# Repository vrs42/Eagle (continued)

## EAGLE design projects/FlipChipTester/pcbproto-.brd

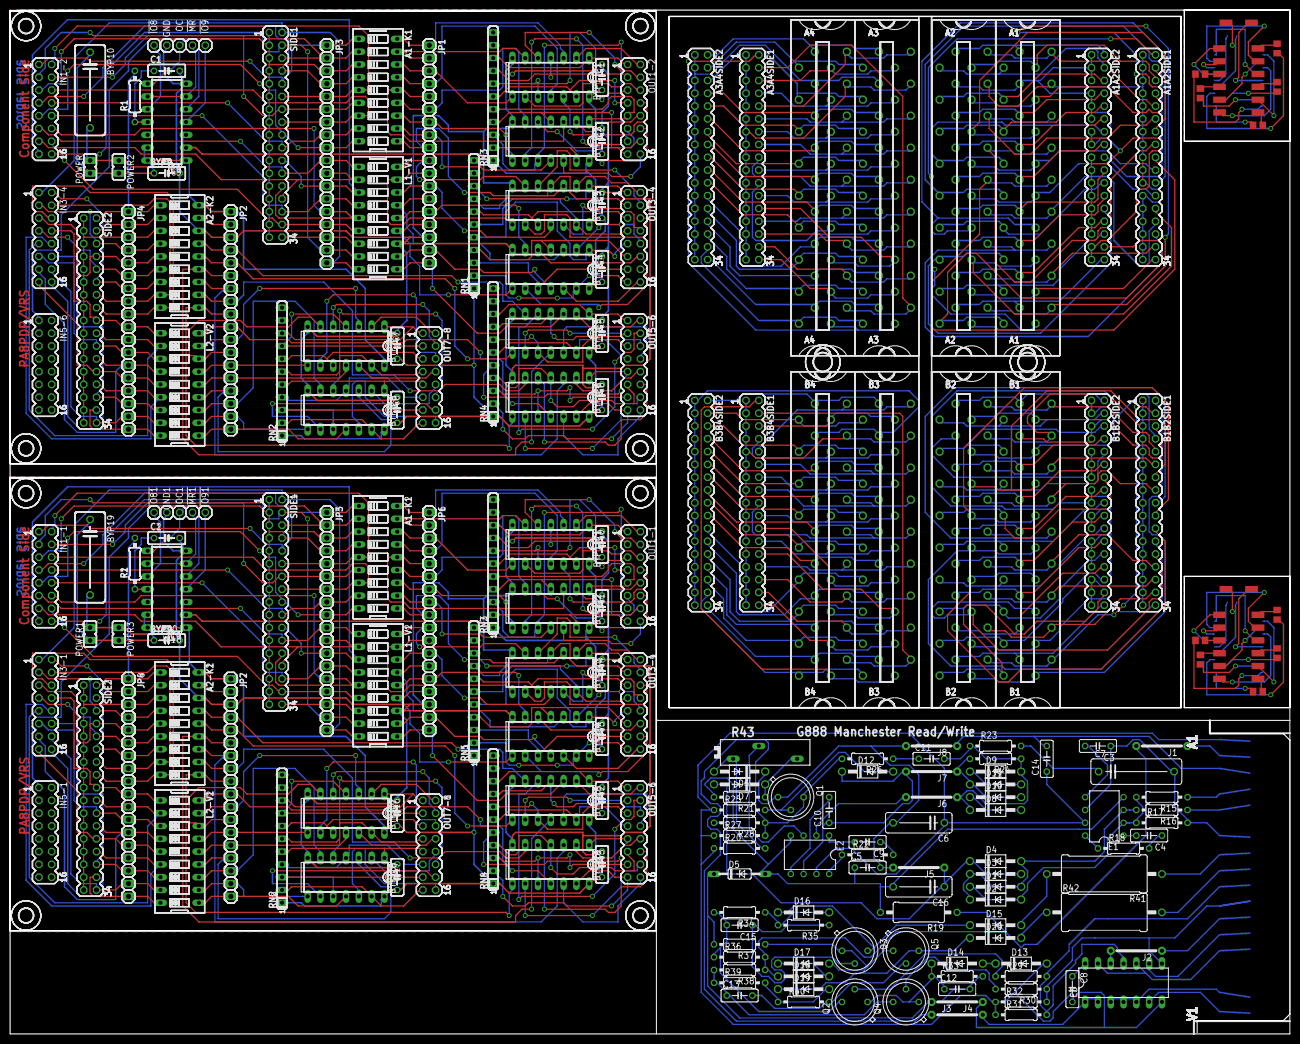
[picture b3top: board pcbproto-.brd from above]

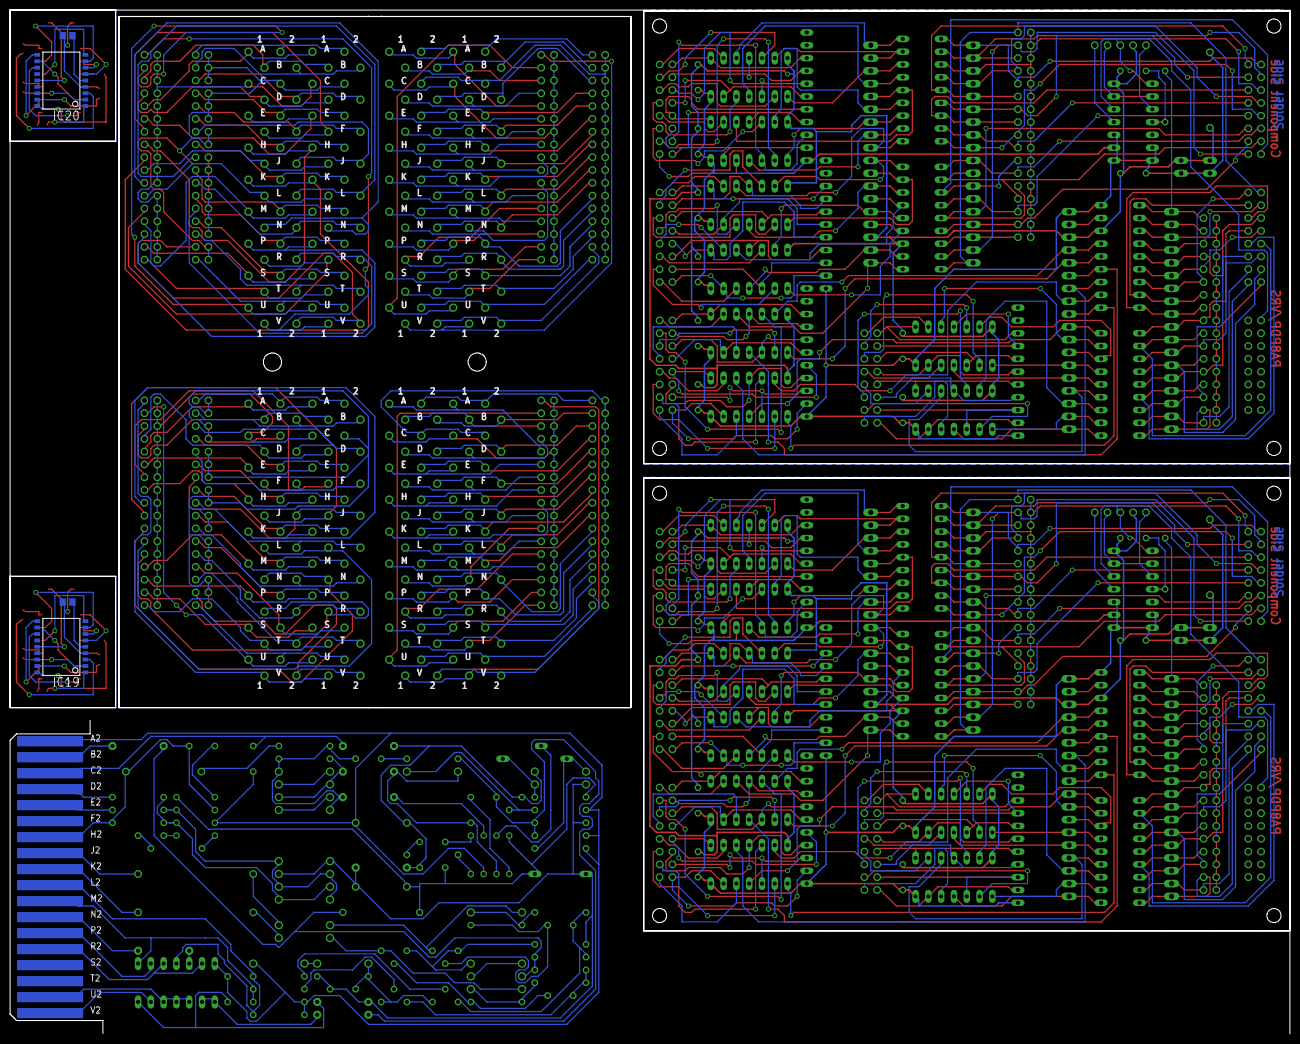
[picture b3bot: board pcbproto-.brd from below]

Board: 2 copper layers, 254.0 x 203.2 mm, 246 parts (4 on the bottom side), 520 nets.

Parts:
!IO8, !IO81: !IO8; 1X01
!IO9, !IO91: !IO9; 1X01
!MR, !MR1: !MR; 1X01
A1, A2, A3, A4: H807
A1-K1, A1-K2: A1-K1; EDG-09
A1A2SIDE1, A1A2SIDE2, A3A4SIDE1, A3A4SIDE2: MA17-2
A2-K1, A2-K2: A2-K2; EDG-09
B1, B2, B3, B4: H807
B1B2SIDE1, B1B2SIDE2, B3B4SIDE1, B3B4SIDE2: MA17-2
BYP1, BYP2, BYP3, BYP4, BYP5, BYP6, BYP7, BYP8, BYP9, BYP11, BYP12, BYP13, BYP14, BYP15, BYP16, BYP17, BYP18, BYP20: 0.1uf; C050-025X075
BYP10, BYP19: 100uf 25V; C150-064X183
C1, C2: 0.1uf; C050-025X075
C3, C5, C8, C10, C11, C12, C14: .01uf; C050-025X075
C4, C9: .22uf; C050-025X075
C6, C16: 6.8uf 35V; C102-043X133
C7: .01uf MYLAR 10%; C150-054X183
C13, C15: .1uf; C050-025X075
D1, D2, D3, D4, D8, D9, D10, D11, D12: 1N3606; DO41-10
D5: 1N753A; DO35Z10
D6, D7, D13, D14, D17, D18: 1N645; DO41-10
D15, D16, D19, D20: D670; DO41-10
E1, E2: MC1709; DIL08
E3: 7400N; DIL14
GND, GND1: GND; 1X01
IC1, IC2, IC3, IC4, IC5, IC6, IC7, IC8, IC10, IC11, IC12, IC13, IC14, IC15, IC16, IC17: 74LS125N; DIL14
IC9, IC18: 74LS10N; DIL14
IC19, IC20: PIC16F627SO; SO-18W
IN1-1, IN1-2, IN3-1, IN3-4, IN5-1, IN5-6: MA08-2
J1, J2, J3, J4, J5, J6, J7, J8: J10MM; 10
JP1, JP2, JP3, JP4, JP5, JP6, JP7, JP8: 1X18
L1-V1, L1-V2: L1-V1; EDG-09
L2-V1, L2-V2: L2-V2; EDG-09
OC, OC1: OC; 1X01
OUT1-1, OUT1-2, OUT3-1, OUT3-4, OUT5-1, OUT5-6, OUT7-1, OUT7-8: MA08-2
PAD1, PAD2, PAD3, PAD4, PAD5, PAD6, PAD7, PAD8, PAD9, PAD10, PAD11, PAD12, PAD13, PAD14, PAD15, PAD16, PAD17, PAD18, PAD19, PAD20, PAD21, PAD22, PAD23, PAD24, PAD25, PAD26, PAD27, PAD28: SMD2
POWER, POWER1, POWER2, POWER3: POWER; JP1
Q1: 2n3009B; TO39
Q2, Q4: MPS6534; TO39
Q3, Q5: MM1008; TO39
R1, R2, R20, R21, R27, R31, R32, R36, R37, R38: 1K; 0207/10
R3, R4, R5, R6, R7, R8, R9, R10, R11, R12, R13, R14: R0805
R15, R16: 220; 0207/10
R17: 22K; 0207/10
R18, R22: 1.5K; 0207/10
R19: 330 1/2W; 0411/15
R23, R25: 4.7K; 0207/10
R24, R26: 470K; 0207/10
R28: 3K; 0207/10
R29, R30, R33: 470; 0207/10
R34, R39: 750; 0207/10
R35, R40: 560; 0207/10
R41, R42: 68 2W; P0817/22
R43: 5K; PT-SPIN
RN1, RN2, RN3, RN4, RN5, RN6, RN7, RN8: SIL11
SIDE1, SIDE2, SIDE3, SIDE4: MA17-2
U$1, U$2, U$3, U$4, U$7, U$8, U$9, U$10: 2,8
U$5, U$6: 3,6
U$11: EDGE-1; EDGE-CON1

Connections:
!C1: IC19.17, R3.1
!C2: IC19.18, R4.1
!C3: IC19.1, R5.1
!C4: IC19.2, R6.1
!C5: IC19.3, R7.1
!C11: IC20.17, R9.1
!C21: IC20.18, R10.1
!C31: IC20.1, R11.1
!C41: IC20.2, R12.1
!C51: IC20.3, R13.1
!COL1: PAD4.1, R3.2
!COL2: PAD3.1, R4.2
!COL3: PAD7.1, R5.2
!COL4: PAD9.1, R6.2
!COL5: PAD12.1, R7.2
!COL11: PAD20.1, R9.2
!COL21: PAD17.1, R10.2
!COL31: PAD21.1, R11.2
!COL41: PAD23.1, R12.2
!COL51: PAD24.1, R13.2
!IO8: !IO8.1, IC9.10
!IO9: !IO9.1, IC9.4
!IO81: !IO81.1, IC18.10
!IO91: !IO91.1, IC18.4
!MR: !MR.1, IC9.6, IC9.9
!MR1: !MR1.1, IC18.6, IC18.9
!STEM: IC19.4, PAD15.1, R8.1
!STEM1: IC20.4, PAD27.1, R14.1
-15V: D18.C, J1.2, R19.1, R36.2, R38.1
A1: A1-K1.1, IN1-2.1, JP3.1, SIDE1.10
A2: A2-K2.1, JP4.1, R1.2, SIDE2.2
A3: A1-K2.1, IN1-1.1, JP5.1, SIDE4.10
A4: A2-K1.1, JP8.1, R2.2, SIDE3.2
B1: A1-K1.2, IN1-2.3, JP3.2, SIDE1.6
B2: A2-K2.2, JP4.2, SIDE2.4
B3: A1-K2.2, IN1-1.3, JP5.2, SIDE4.6
B4: A2-K1.2, JP8.2, SIDE3.4
C1: A1-K1.3, IN1-2.5, JP3.3, SIDE1.1, SIDE1.3, SIDE1.5, SIDE1.7, SIDE1.9, SIDE1.11, SIDE1.13, SIDE1.15, SIDE1.17, SIDE1.19, SIDE1.21, SIDE1.23, SIDE1.25, SIDE1.27, SIDE1.29, SIDE1.31, SIDE1.33
C2: A2-K2.3, JP4.3, SIDE2.1, SIDE2.3, SIDE2.5, SIDE2.7, SIDE2.9, SIDE2.11, SIDE2.13, SIDE2.15, SIDE2.17, SIDE2.19, SIDE2.21, SIDE2.23, SIDE2.25, SIDE2.27, SIDE2.29, SIDE2.31, SIDE2.33
C3: A1-K2.3, IN1-1.5, JP5.3, SIDE4.1, SIDE4.3, SIDE4.5, SIDE4.7, SIDE4.9, SIDE4.11, SIDE4.13, SIDE4.15, SIDE4.17, SIDE4.19, SIDE4.21, SIDE4.23, SIDE4.25, SIDE4.27, SIDE4.29, SIDE4.31, SIDE4.33
C4: A2-K1.3, JP8.3, SIDE3.1, SIDE3.3, SIDE3.5, SIDE3.7, SIDE3.9, SIDE3.11, SIDE3.13, SIDE3.15, SIDE3.17, SIDE3.19, SIDE3.21, SIDE3.23, SIDE3.25, SIDE3.27, SIDE3.29, SIDE3.31, SIDE3.33
D: R15.1, U$11.D2
D1: A1-K1.4, IN1-2.7, JP3.4, SIDE1.8
D2: A2-K2.4, IN3-4.3, JP4.4, SIDE2.6
D3: A1-K2.4, IN1-1.7, JP5.4, SIDE4.8
D4: A2-K1.4, IN3-1.3, JP8.4, SIDE3.6
E: R16.1, U$11.E2
E1: A1-K1.5, IN1-2.2, JP3.5, SIDE1.12
E2: A2-K2.5, IN3-4.5, JP4.5, SIDE2.8
E3: A1-K2.5, IN1-1.2, JP5.5, SIDE4.12
E4: A2-K1.5, IN3-1.5, JP8.5, SIDE3.8
F1: A1-K1.6, IN1-2.4, JP3.6, SIDE1.14
F2: A2-K2.6, IN3-4.7, JP4.6, SIDE2.10
F3: A2-K1.6, IN3-1.7, JP8.6, SIDE3.10
F4: A1-K2.6, IN1-1.4, JP5.6, SIDE4.14
GND: A2-K2.16, BYP1.2, BYP2.2, BYP3.2, BYP4.2, BYP5.2, BYP6.2, BYP7.2, BYP8.2, BYP9.2, BYP10.2, C1.2, GND.1, IC1.7, IC2.7, IC3.7, IC4.7, IC5.7, IC6.7, IC7.7, IC8.7, IC9.7, JP1.16, JP2.3, L1-V1.12, POWER.1, POWER2.1
GND1: A2-K1.16, BYP11.2, BYP12.2, BYP13.2, BYP14.2, BYP15.2, BYP16.2, BYP17.2, BYP18.2, BYP19.2, BYP20.2, C2.2, GND1.1, IC10.7, IC11.7, IC12.7, IC13.7, IC14.7, IC15.7, IC16.7, IC17.7, IC18.7, JP6.16, JP7.3, L1-V2.12, POWER1.1, POWER3.1
GND2: IC19.5, R8.2
GND3: IC20.5, R14.2
GND4: C5.2, C6.2, C8.2, C12.2, C14.2, C16.1, D3.A, D4.C, D5.C, D6.C, D7.A, E3.7, J4.1, J4.2, J5.1, J5.2, J8.1, J8.2, Q1.1, R28.2, R33.2, R37.2, U$11.C2
H: C3.1, C7.2, E1.6, R17.2, U$11.H2
H1: A1-K1.7, IN1-2.6, JP3.7, SIDE1.16
H2: A2-K2.7, IN3-4.2, JP4.7, SIDE2.12
H3: A1-K2.7, IN1-1.6, JP5.7, SIDE4.16
H4: A2-K1.7, IN3-1.2, JP8.7, SIDE3.12
J: R41.1, U$11.J2
J1: A1-K1.8, IN1-2.8, JP3.8, SIDE1.20
J2: A2-K2.8, IN3-4.4, JP4.8, SIDE2.14
J3: A1-K2.8, IN1-1.8, JP5.8, SIDE4.20
J4: A2-K1.8, IN3-1.4, JP8.8, SIDE3.14
K: R42.2, U$11.K2
K1: A1-K1.9, IN1-2.9, JP3.9, SIDE1.18
K2: A2-K2.9, IN3-4.6, JP4.9, SIDE2.16
K3: A2-K1.9, IN3-1.6, JP8.9, SIDE3.16
K4: A1-K2.9, IN1-1.9, JP5.9, SIDE4.18
L: E3.11, R29.2, R31.2, U$11.L2
L1: IN1-2.11, JP3.10, L1-V1.1, SIDE1.24
L2: IN3-4.8, JP4.10, L2-V2.1, SIDE2.18
L3: IN1-1.11, JP5.10, L1-V2.1, SIDE4.24
L4: IN3-1.8, JP8.10, L2-V1.1, SIDE3.18
M: E3.8, R30.1, R32.2, U$11.M2
M1: IN1-2.13, JP3.11, L1-V1.2, SIDE1.28
M2: IN3-4.9, JP4.11, L2-V2.2, SIDE2.20
M3: IN1-1.13, JP5.11, L1-V2.2, SIDE4.28
M4: IN3-1.9, JP8.11, L2-V1.2, SIDE3.20
N: J2.1, U$11.N2
N1: IN1-2.15, JP3.12, L1-V1.3, SIDE1.22
N2: IN3-4.11, JP4.12, L2-V2.3, SIDE2.22
N3: IN3-1.11, JP8.12, L2-V1.3, SIDE3.22
N4: IN1-1.15, JP5.12, L1-V2.3, SIDE4.22
unnamed: B1.C2, B1B2SIDE2.1, B1B2SIDE2.3, B1B2SIDE2.5, B1B2SIDE2.7, B1B2SIDE2.9, B1B2SIDE2.11, B1B2SIDE2.13, B1B2SIDE2.15, B1B2SIDE2.17, B1B2SIDE2.19, B1B2SIDE2.21, B1B2SIDE2.23, B1B2SIDE2.25, B1B2SIDE2.27, B1B2SIDE2.29, B1B2SIDE2.31, B1B2SIDE2.33, B2.C2
unnamed: B1.A2, B1B2SIDE2.2, B2.A2
unnamed: B1.B2, B1B2SIDE2.4, B2.B2
unnamed: B1.D2, B1B2SIDE2.6, B2.D2
unnamed: B1.E2, B1B2SIDE2.8, B2.E2
unnamed: B1.F2, B1B2SIDE2.10, B2.F2
unnamed: B1.H2, B1B2SIDE2.12, B2.H2
unnamed: B1.J2, B1B2SIDE2.14, B2.J2
unnamed: B1.K2, B1B2SIDE2.16, B2.K2
unnamed: B1.L2, B1B2SIDE2.18, B2.L2
unnamed: B1.M2, B1B2SIDE2.20, B2.M2
unnamed: B1.N2, B1B2SIDE2.22, B2.N2
unnamed: B1.P2, B1B2SIDE2.24, B2.P2
unnamed: B1.R2, B1B2SIDE2.26, B2.R2
unnamed: B1.S2, B1B2SIDE2.28, B2.S2
unnamed: B1.T2, B1B2SIDE2.30, B2.T2
unnamed: B1.U2, B1B2SIDE2.34, B2.U2
unnamed: B1.V2, B1B2SIDE2.32, B2.V2
unnamed: B1.A1, B1B2SIDE1.10, B2.A1
unnamed: B1.B1, B1B2SIDE1.6, B2.B1
unnamed: B1.D1, B1B2SIDE1.8, B2.D1
unnamed: B1.E1, B1B2SIDE1.12, B2.E1
unnamed: B1.F1, B1B2SIDE1.14, B2.F1
unnamed: B1.H1, B1B2SIDE1.16, B2.H1
unnamed: B1.J1, B1B2SIDE1.20, B2.J1
unnamed: B1.K1, B1B2SIDE1.18, B2.K1
unnamed: B1.L1, B1B2SIDE1.24, B2.L1
unnamed: B1.M1, B1B2SIDE1.28, B2.M1
unnamed: B1.N1, B1B2SIDE1.22, B2.N1
unnamed: B1.P1, B1B2SIDE1.30, B2.P1
unnamed: B1.R1, B1B2SIDE1.26, B2.R1
unnamed: B1.S1, B1B2SIDE1.32, B2.S1
unnamed: B1.T1, B1B2SIDE1.34, B2.T1
unnamed: B1.U1, B1B2SIDE1.4, B2.U1
unnamed: B1.V1, B1B2SIDE1.2, B2.V1
unnamed: B1.C1, B1B2SIDE1.1, B1B2SIDE1.3, B1B2SIDE1.5, B1B2SIDE1.7, B1B2SIDE1.9, B1B2SIDE1.11, B1B2SIDE1.13, B1B2SIDE1.15, B1B2SIDE1.17, B1B2SIDE1.19, B1B2SIDE1.21, B1B2SIDE1.23, B1B2SIDE1.25, B1B2SIDE1.27, B1B2SIDE1.29, B1B2SIDE1.31, B1B2SIDE1.33, B2.C1
unnamed: A1.C2, A1A2SIDE2.1, A1A2SIDE2.3, A1A2SIDE2.5, A1A2SIDE2.7, A1A2SIDE2.9, A1A2SIDE2.11, A1A2SIDE2.13, A1A2SIDE2.15, A1A2SIDE2.17, A1A2SIDE2.19, A1A2SIDE2.21, A1A2SIDE2.23, A1A2SIDE2.25, A1A2SIDE2.27, A1A2SIDE2.29, A1A2SIDE2.31, A1A2SIDE2.33, A2.C2
unnamed: A1.A2, A1A2SIDE2.2, A2.A2
unnamed: A1.B2, A1A2SIDE2.4, A2.B2
unnamed: A1.D2, A1A2SIDE2.6, A2.D2
unnamed: A1.E2, A1A2SIDE2.8, A2.E2
unnamed: A1.F2, A1A2SIDE2.10, A2.F2
unnamed: A1.H2, A1A2SIDE2.12, A2.H2
unnamed: A1.J2, A1A2SIDE2.14, A2.J2
unnamed: A1.K2, A1A2SIDE2.16, A2.K2
unnamed: A1.L2, A1A2SIDE2.18, A2.L2
unnamed: A1.M2, A1A2SIDE2.20, A2.M2
unnamed: A1.N2, A1A2SIDE2.22, A2.N2
unnamed: A1.P2, A1A2SIDE2.24, A2.P2
unnamed: A1.R2, A1A2SIDE2.26, A2.R2
unnamed: A1.S2, A1A2SIDE2.28, A2.S2
unnamed: A1.T2, A1A2SIDE2.30, A2.T2
unnamed: A1.U2, A1A2SIDE2.34, A2.U2
unnamed: A1.V2, A1A2SIDE2.32, A2.V2
unnamed: A1.A1, A1A2SIDE1.10, A2.A1
unnamed: A1.B1, A1A2SIDE1.6, A2.B1
unnamed: A1.D1, A1A2SIDE1.8, A2.D1
unnamed: A1.E1, A1A2SIDE1.12, A2.E1
unnamed: A1.F1, A1A2SIDE1.14, A2.F1
unnamed: A1.H1, A1A2SIDE1.16, A2.H1
unnamed: A1.J1, A1A2SIDE1.20, A2.J1
unnamed: A1.K1, A1A2SIDE1.18, A2.K1
unnamed: A1.L1, A1A2SIDE1.24, A2.L1
unnamed: A1.M1, A1A2SIDE1.28, A2.M1
unnamed: A1.N1, A1A2SIDE1.22, A2.N1
unnamed: A1.P1, A1A2SIDE1.30, A2.P1
unnamed: A1.R1, A1A2SIDE1.26, A2.R1
unnamed: A1.S1, A1A2SIDE1.32, A2.S1
unnamed: A1.T1, A1A2SIDE1.34, A2.T1
unnamed: A1.U1, A1A2SIDE1.4, A2.U1
unnamed: A1.V1, A1A2SIDE1.2, A2.V1
unnamed: A1.C1, A1A2SIDE1.1, A1A2SIDE1.3, A1A2SIDE1.5, A1A2SIDE1.7, A1A2SIDE1.9, A1A2SIDE1.11, A1A2SIDE1.13, A1A2SIDE1.15, A1A2SIDE1.17, A1A2SIDE1.19, A1A2SIDE1.21, A1A2SIDE1.23, A1A2SIDE1.25, A1A2SIDE1.27, A1A2SIDE1.29, A1A2SIDE1.31, A1A2SIDE1.33, A2.C1
unnamed: IC1.4, OUT1-2.3, RN3.8
unnamed: IC1.13, OUT1-2.7, RN3.6
unnamed: IC1.2, OUT1-2.2
unnamed: IC1.5, OUT1-2.4
unnamed: IC1.9, OUT1-2.6
unnamed: IC1.12, OUT1-2.8
unnamed: IC2.10, OUT1-2.13, RN3.3
unnamed: IC2.4, OUT1-2.11, RN3.4
unnamed: IC2.1, OUT1-2.9, RN3.5
unnamed: IC2.2, OUT1-2.10
unnamed: IC2.9, OUT1-2.14
unnamed: IC2.12, OUT1-2.16
unnamed: IC1.1, OUT1-2.1, RN3.9
unnamed: IC1.10, OUT1-2.5, RN3.7
unnamed: IC2.5, OUT1-2.12
unnamed: IC5.4, OUT5-6.3, RN4.8
unnamed: IC6.4, OUT5-6.11, RN4.4
unnamed: IC6.1, OUT5-6.9, RN4.5
unnamed: IC6.2, OUT5-6.10
unnamed: IC6.9, OUT5-6.14
unnamed: IC6.12, OUT5-6.16
unnamed: IC5.1, OUT5-6.1, RN4.9
unnamed: IC5.10, OUT5-6.5, RN4.7
unnamed: IC6.5, OUT5-6.12
unnamed: IC6.13, OUT5-6.15, RN4.2
unnamed: IC3.4, OUT3-4.3, RN1.8
unnamed: IC3.13, OUT3-4.7, RN1.6
unnamed: IC3.2, OUT3-4.2
unnamed: IC3.5, OUT3-4.4
unnamed: IC3.9, OUT3-4.6
unnamed: IC3.12, OUT3-4.8
unnamed: IC4.10, OUT3-4.13, RN1.3
unnamed: IC4.4, OUT3-4.11, RN1.4
unnamed: IC4.1, OUT3-4.9, RN1.5
unnamed: IC4.2, OUT3-4.10
unnamed: IC4.9, OUT3-4.14
unnamed: IC4.12, OUT3-4.16
unnamed: IC3.1, OUT3-4.1, RN1.9
unnamed: IC3.10, OUT3-4.5, RN1.7
unnamed: IC4.5, OUT3-4.12
unnamed: IC4.13, OUT3-4.15, RN1.2
unnamed: IC7.4, OUT7-8.3, RN2.8
unnamed: IC7.13, OUT7-8.7, RN2.6
unnamed: IC7.2, OUT7-8.2
unnamed: IC7.5, OUT7-8.4
unnamed: IC7.9, OUT7-8.6
unnamed: IC7.12, OUT7-8.8
unnamed: IC8.10, OUT7-8.13, RN2.3
unnamed: IC8.4, OUT7-8.11, RN2.4
unnamed: IC8.1, OUT7-8.9, RN2.5
unnamed: IC8.2, OUT7-8.10
unnamed: IC8.9, OUT7-8.14
unnamed: C1.1, IC9.11, R1.1
unnamed: IC10.4, OUT1-1.3, RN7.8
unnamed: IC10.13, OUT1-1.7, RN7.6
unnamed: IC10.2, OUT1-1.2
unnamed: IC10.5, OUT1-1.4
unnamed: IC10.9, OUT1-1.6
unnamed: IC10.12, OUT1-1.8
unnamed: IC11.10, OUT1-1.13, RN7.3
unnamed: IC11.4, OUT1-1.11, RN7.4
unnamed: IC11.1, OUT1-1.9, RN7.5
unnamed: IC11.2, OUT1-1.10
unnamed: IC11.9, OUT1-1.14
unnamed: IC11.12, OUT1-1.16
unnamed: IC5.13, OUT5-6.7, RN4.6
unnamed: IC2.13, OUT1-2.15, RN3.2
unnamed: IC5.2, OUT5-6.2
unnamed: IC5.5, OUT5-6.4
unnamed: IC5.9, OUT5-6.6
unnamed: IC5.12, OUT5-6.8
unnamed: IC6.10, OUT5-6.13, RN4.3
unnamed: A3.C2, A3A4SIDE2.1, A3A4SIDE2.3, A3A4SIDE2.5, A3A4SIDE2.7, A3A4SIDE2.9, A3A4SIDE2.11, A3A4SIDE2.13, A3A4SIDE2.15, A3A4SIDE2.17, A3A4SIDE2.19, A3A4SIDE2.21, A3A4SIDE2.23, A3A4SIDE2.25, A3A4SIDE2.27, A3A4SIDE2.29, A3A4SIDE2.31, A3A4SIDE2.33, A4.C2
unnamed: A3.A2, A3A4SIDE2.2, A4.A2
unnamed: A3.B2, A3A4SIDE2.4, A4.B2
unnamed: A3.D2, A3A4SIDE2.6, A4.D2
unnamed: A3.E2, A3A4SIDE2.8, A4.E2
unnamed: A3.F2, A3A4SIDE2.10, A4.F2
unnamed: A3.H2, A3A4SIDE2.12, A4.H2
unnamed: A3.J2, A3A4SIDE2.14, A4.J2
unnamed: A3.K2, A3A4SIDE2.16, A4.K2
unnamed: A3.L2, A3A4SIDE2.18, A4.L2
unnamed: A3.M2, A3A4SIDE2.20, A4.M2
unnamed: A3.N2, A3A4SIDE2.22, A4.N2
unnamed: A3.P2, A3A4SIDE2.24, A4.P2
unnamed: A3.R2, A3A4SIDE2.26, A4.R2
unnamed: A3.S2, A3A4SIDE2.28, A4.S2
unnamed: A3.T2, A3A4SIDE2.30, A4.T2
unnamed: A3.U2, A3A4SIDE2.34, A4.U2
unnamed: A3.V2, A3A4SIDE2.32, A4.V2
unnamed: A3.A1, A3A4SIDE1.10, A4.A1
unnamed: A3.B1, A3A4SIDE1.6, A4.B1
unnamed: A3.D1, A3A4SIDE1.8, A4.D1
unnamed: A3.E1, A3A4SIDE1.12, A4.E1
unnamed: A3.F1, A3A4SIDE1.14, A4.F1
unnamed: A3.H1, A3A4SIDE1.16, A4.H1
unnamed: A3.J1, A3A4SIDE1.20, A4.J1
unnamed: A3.K1, A3A4SIDE1.18, A4.K1
unnamed: A3.L1, A3A4SIDE1.24, A4.L1
unnamed: A3.M1, A3A4SIDE1.28, A4.M1
unnamed: A3.N1, A3A4SIDE1.22, A4.N1
unnamed: A3.P1, A3A4SIDE1.30, A4.P1
unnamed: A3.R1, A3A4SIDE1.26, A4.R1
unnamed: A3.S1, A3A4SIDE1.32, A4.S1
unnamed: A3.T1, A3A4SIDE1.34, A4.T1
unnamed: A3.U1, A3A4SIDE1.4, A4.U1
unnamed: A3.V1, A3A4SIDE1.2, A4.V1
unnamed: A3.C1, A3A4SIDE1.1, A3A4SIDE1.3, A3A4SIDE1.5, A3A4SIDE1.7, A3A4SIDE1.9, A3A4SIDE1.11, A3A4SIDE1.13, A3A4SIDE1.15, A3A4SIDE1.17, A3A4SIDE1.19, A3A4SIDE1.21, A3A4SIDE1.23, A3A4SIDE1.25, A3A4SIDE1.27, A3A4SIDE1.29, A3A4SIDE1.31, A3A4SIDE1.33, A4.C1
unnamed: IC8.12, OUT7-8.16
unnamed: IC7.1, OUT7-8.1, RN2.9
unnamed: IC7.10, OUT7-8.5, RN2.7
unnamed: IC8.5, OUT7-8.12
unnamed: IC8.13, OUT7-8.15, RN2.2
unnamed: IC10.1, OUT1-1.1, RN7.9
unnamed: IC10.10, OUT1-1.5, RN7.7
unnamed: IC11.5, OUT1-1.12
unnamed: IC11.13, OUT1-1.15, RN7.2
unnamed: IC12.4, OUT5-1.3, RN8.8
unnamed: IC12.13, OUT5-1.7, RN8.6
unnamed: IC12.2, OUT5-1.2
unnamed: IC12.5, OUT5-1.4
unnamed: IC12.9, OUT5-1.6
unnamed: IC12.12, OUT5-1.8
unnamed: IC13.10, OUT5-1.13, RN8.3
unnamed: IC13.4, OUT5-1.11, RN8.4
unnamed: IC13.1, OUT5-1.9, RN8.5
unnamed: IC13.2, OUT5-1.10
unnamed: IC13.9, OUT5-1.14
unnamed: IC13.12, OUT5-1.16
unnamed: IC12.1, OUT5-1.1, RN8.9
unnamed: IC12.10, OUT5-1.5, RN8.7
unnamed: IC13.5, OUT5-1.12
unnamed: IC13.13, OUT5-1.15, RN8.2
unnamed: IC14.4, OUT3-1.3, RN5.8
unnamed: IC14.13, OUT3-1.7, RN5.6
unnamed: IC14.2, OUT3-1.2
unnamed: IC14.5, OUT3-1.4
unnamed: IC14.9, OUT3-1.6
unnamed: IC14.12, OUT3-1.8
unnamed: IC15.10, OUT3-1.13, RN5.3
unnamed: IC15.4, OUT3-1.11, RN5.4
unnamed: IC15.1, OUT3-1.9, RN5.5
unnamed: IC15.2, OUT3-1.10
unnamed: IC15.9, OUT3-1.14
unnamed: IC15.12, OUT3-1.16
unnamed: IC14.1, OUT3-1.1, RN5.9
unnamed: IC14.10, OUT3-1.5, RN5.7
unnamed: IC15.5, OUT3-1.12
unnamed: IC15.13, OUT3-1.15, RN5.2
unnamed: IC16.4, OUT7-1.3, RN6.8
unnamed: IC16.13, OUT7-1.7, RN6.6
unnamed: IC16.2, OUT7-1.2
unnamed: IC16.5, OUT7-1.4
unnamed: IC16.9, OUT7-1.6
unnamed: IC16.12, OUT7-1.8
unnamed: IC17.10, OUT7-1.13, RN6.3
unnamed: IC17.4, OUT7-1.11, RN6.4
unnamed: IC17.1, OUT7-1.9, RN6.5
unnamed: IC17.2, OUT7-1.10
unnamed: IC17.9, OUT7-1.14
unnamed: IC17.12, OUT7-1.16
unnamed: IC16.1, OUT7-1.1, RN6.9
unnamed: IC16.10, OUT7-1.5, RN6.7
unnamed: IC17.5, OUT7-1.12
unnamed: IC17.13, OUT7-1.15, RN6.2
unnamed: C2.1, IC18.11, R2.1
unnamed: D1.C, D2.A, E1.2, R15.2, R17.1
unnamed: D1.A, D2.C, D3.C, D4.A, E1.3, R16.2
unnamed: C4.2, E1.1
unnamed: E1.8, R18.1
unnamed: C3.2, E1.5
unnamed: C4.1, R18.2
unnamed: D6.A, R20.2, R43.A
unnamed: E2.3, R43.S
unnamed: D7.C, R21.1, R43.E
unnamed: C9.1, R22.2
unnamed: C9.2, E2.1
unnamed: E2.8, R22.1
unnamed: C10.2, E2.5
unnamed: C7.1, R23.2
unnamed: B3.C2, B3B4SIDE2.1, B3B4SIDE2.3, B3B4SIDE2.5, B3B4SIDE2.7, B3B4SIDE2.9, B3B4SIDE2.11, B3B4SIDE2.13, B3B4SIDE2.15, B3B4SIDE2.17, B3B4SIDE2.19, B3B4SIDE2.21, B3B4SIDE2.23, B3B4SIDE2.25, B3B4SIDE2.27, B3B4SIDE2.29, B3B4SIDE2.31, B3B4SIDE2.33, B4.C2
unnamed: B3.A2, B3B4SIDE2.2, B4.A2
unnamed: B3.B2, B3B4SIDE2.4, B4.B2
unnamed: B3.D2, B3B4SIDE2.6, B4.D2
unnamed: B3.E2, B3B4SIDE2.8, B4.E2
unnamed: B3.F2, B3B4SIDE2.10, B4.F2
unnamed: B3.H2, B3B4SIDE2.12, B4.H2
unnamed: B3.J2, B3B4SIDE2.14, B4.J2
unnamed: B3.K2, B3B4SIDE2.16, B4.K2
unnamed: B3.L2, B3B4SIDE2.18, B4.L2
unnamed: B3.M2, B3B4SIDE2.20, B4.M2
unnamed: B3.N2, B3B4SIDE2.22, B4.N2
unnamed: B3.P2, B3B4SIDE2.24, B4.P2
unnamed: B3.R2, B3B4SIDE2.26, B4.R2
unnamed: B3.S2, B3B4SIDE2.28, B4.S2
unnamed: B3.T2, B3B4SIDE2.30, B4.T2
unnamed: B3.U2, B3B4SIDE2.34, B4.U2
unnamed: B3.V2, B3B4SIDE2.32, B4.V2
unnamed: B3.A1, B3B4SIDE1.10, B4.A1
unnamed: B3.B1, B3B4SIDE1.6, B4.B1
unnamed: B3.D1, B3B4SIDE1.8, B4.D1
unnamed: B3.E1, B3B4SIDE1.12, B4.E1
unnamed: B3.F1, B3B4SIDE1.14, B4.F1
unnamed: B3.H1, B3B4SIDE1.16, B4.H1
unnamed: B3.J1, B3B4SIDE1.20, B4.J1
unnamed: B3.K1, B3B4SIDE1.18, B4.K1
unnamed: B3.L1, B3B4SIDE1.24, B4.L1
unnamed: B3.M1, B3B4SIDE1.28, B4.M1
unnamed: B3.N1, B3B4SIDE1.22, B4.N1
unnamed: B3.P1, B3B4SIDE1.30, B4.P1
unnamed: B3.R1, B3B4SIDE1.26, B4.R1
unnamed: B3.S1, B3B4SIDE1.32, B4.S1
unnamed: B3.T1, B3B4SIDE1.34, B4.T1
unnamed: B3.U1, B3B4SIDE1.4, B4.U1
unnamed: B3.V1, B3B4SIDE1.2, B4.V1
unnamed: B3.C1, B3B4SIDE1.1, B3B4SIDE1.3, B3B4SIDE1.5, B3B4SIDE1.7, B3B4SIDE1.9, B3B4SIDE1.11, B3B4SIDE1.13, B3B4SIDE1.15, B3B4SIDE1.17, B3B4SIDE1.19, B3B4SIDE1.21, B3B4SIDE1.23, B3B4SIDE1.25, B3B4SIDE1.27, B3B4SIDE1.29, B3B4SIDE1.31, B3B4SIDE1.33, B4.C1
unnamed: D9.C, D11.A
unnamed: D8.A, D10.C
unnamed: C10.1, D10.A, D11.C, D12.C, E2.6, J7.1, J7.2, R24.2
unnamed: C11.2, D8.C, D9.A, E2.2, J6.1, J6.2, R23.1, R24.1
unnamed: C11.1, R26.1
unnamed: D12.A, Q1.2, R25.2
unnamed: J3.1, Q1.3, R26.2, R27.2, R28.1
unnamed: D17.A, Q3.1, Q5.1, R37.1
unnamed: C12.1, D14.C, Q2.1, Q4.1, R33.1
unnamed: D13.C, D14.A
unnamed: D16.A, R34.1, R35.2
unnamed: C15.2, Q2.3, R34.2, R36.1
unnamed: C15.1, Q3.2, R35.1
unnamed: D19.A, R39.2, R40.1
unnamed: C13.1, Q4.3, R38.2, R39.1
unnamed: C13.2, Q5.2, R40.2
unnamed: D15.C, D16.C, Q3.3
unnamed: D19.C, D20.C, Q5.3
unnamed: D17.C, D18.A
unnamed: D15.A, R41.2
unnamed: D20.A, R42.1
unnamed: E3.12, J2.2
unnamed: Q2.2, R29.1
unnamed: Q4.2, R30.2
unnamed: J1.1, U$11.B2
unnamed: E3.1, E3.2, J3.2
OA1: A1-K1.18, IC1.3, JP1.1
OA2: A1-K2.18, IC10.3, JP6.1
OB1: A1-K1.17, IC1.6, JP1.2
OB2: A2-K2.17, JP2.2
OB3: A1-K2.17, IC10.6, JP6.2
OB4: A2-K1.17, JP7.2
OC: IC9.5, IC9.8, IN5-6.1, OC.1
OC1: A1-K1.16, IC1.8, JP1.3
OC2: A1-K2.16, IC10.8, JP6.3
OC3: IC18.5, IC18.8, IN5-1.1, OC1.1
OD1: A1-K1.15, IC1.11, JP1.4
OD2: A2-K2.15, IC5.6, JP2.4
OD3: A1-K2.15, IC10.11, JP6.4
OD4: A2-K1.15, IC12.6, JP7.4
OE1: A1-K1.14, IC2.3, JP1.5
OE2: A2-K2.14, IC5.8, JP2.5
OE3: A1-K2.14, IC11.3, JP6.5
OE4: A2-K1.14, IC12.8, JP7.5
OF1: A1-K1.13, IC2.6, JP1.6
OF2: A2-K2.13, IC5.11, JP2.6
OF3: A1-K2.13, IC11.6, JP6.6
OF4: A2-K1.13, IC12.11, JP7.6
OH1: A1-K1.12, IC2.8, JP1.7
OH2: A2-K2.12, IC6.3, JP2.7
OH3: A1-K2.12, IC11.8, JP6.7
OH4: A2-K1.12, IC13.3, JP7.7
OJ1: A1-K1.11, IC2.11, JP1.8
OJ2: A2-K2.11, IC6.6, JP2.8
OJ3: A1-K2.11, IC11.11, JP6.8
OJ4: A2-K1.11, IC13.6, JP7.8
OK1: A1-K1.10, IC3.3, JP1.9
OK2: A2-K2.10, IC6.8, JP2.9
OK3: A1-K2.10, IC14.3, JP6.9
OK4: A2-K1.10, IC13.8, JP7.9
OL1: IC3.6, JP1.10, L1-V1.18
OL2: IC6.11, JP2.10, L2-V2.18
OL3: IC14.6, JP6.10, L1-V2.18
OL4: IC13.11, JP7.10, L2-V1.18
OM1: IC3.8, JP1.11, L1-V1.17
OM2: IC7.3, JP2.11, L2-V2.17
OM3: IC14.8, JP6.11, L1-V2.17
OM4: IC16.3, JP7.11, L2-V1.17
ON1: IC3.11, JP1.12, L1-V1.16
ON2: IC7.6, JP2.12, L2-V2.16
ON3: IC14.11, JP6.12, L1-V2.16
ON4: IC16.6, JP7.12, L2-V1.16
OP1: IC4.3, JP1.13, L1-V1.15
OP2: IC7.8, JP2.13, L2-V2.15
OP3: IC15.3, JP6.13, L1-V2.15
OP4: IC16.8, JP7.13, L2-V1.15
OR1: IC4.6, JP1.14, L1-V1.14
OR2: IC7.11, JP2.14, L2-V2.14
OR3: IC15.6, JP6.14, L1-V2.14
OR4: IC16.11, JP7.14, L2-V1.14
OS1: IC4.8, JP1.15, L1-V1.13
OS2: IC8.3, JP2.15, L2-V2.13
OS3: IC15.8, JP6.15, L1-V2.13
OS4: IC17.3, JP7.15, L2-V1.13
OT1: IC17.6, JP7.16, L2-V1.12
OT2: IC8.6, JP2.16, L2-V2.12
OU1: IC4.11, JP1.17, L1-V1.11
OU2: IC8.8, JP2.17, L2-V2.11
OU3: IC15.11, JP6.17, L1-V2.11
OU4: IC17.8, JP7.17, L2-V1.11
OV1: IC5.3, JP1.18, L1-V1.10
OV2: IC8.11, JP2.18, L2-V2.10
OV3: IC12.3, JP6.18, L1-V2.10
OV4: IC17.11, JP7.18, L2-V1.10
P: E3.9, U$11.P2
P1: IN1-2.10, JP3.13, L1-V1.4, SIDE1.30
P2: IN3-4.13, JP4.13, L2-V2.4, SIDE2.24
P3: IN1-1.10, JP5.13, L1-V2.4, SIDE4.30
P4: IN3-1.13, JP8.13, L2-V1.4, SIDE3.24
R: E3.10, E3.13, U$11.R2
R1: IN1-2.12, JP3.14, L1-V1.5, SIDE1.26
R2: IN3-4.15, JP4.14, L2-V2.5, SIDE2.26
R3: IN3-1.15, JP8.14, L2-V1.5, SIDE3.26
R4: IN1-1.12, JP5.14, L1-V2.5, SIDE4.26
ROW1: IC19.6, PAD1.1
ROW2: IC19.7, PAD2.1
ROW3: IC19.8, PAD11.1
ROW4: IC19.9, PAD10.1
ROW5: IC19.10, PAD8.1
ROW6: IC19.11, PAD5.1
ROW7: IC19.12, PAD6.1
ROW8: IC20.6, PAD13.1
ROW9: IC20.7, PAD14.1
ROW10: IC20.11, PAD19.1
ROW11: IC20.12, PAD18.1
ROW12: IC20.8, PAD25.1
ROW13: IC20.9, PAD26.1
ROW14: IC20.10, PAD22.1
S1: IN1-2.14, JP3.15, L1-V1.6, SIDE1.32
S2: IN3-4.10, JP4.15, L2-V2.6, SIDE2.28
S3: IN1-1.14, JP5.15, L1-V2.6, SIDE4.32
S4: IN3-1.10, JP8.15, L2-V1.6, SIDE3.28
T1: JP3.16, L1-V1.7, SIDE1.34
T2: IN3-4.12, JP4.16, L2-V2.7, SIDE2.30
T3: IN3-1.12, JP8.16, L2-V1.7, SIDE3.30
T4: JP5.16, L1-V2.7, SIDE4.34
U: E3.3, E3.4, E3.5, U$11.U2
U1: IN1-2.16, JP3.17, L1-V1.8, SIDE1.4
U2: IN3-4.14, JP4.17, L2-V2.8, SIDE2.34
U3: IN3-1.14, JP8.17, L2-V1.8, SIDE3.34
U4: IN1-1.16, JP5.17, L1-V2.8, SIDE4.4
V: E3.6, U$11.V2
V1: IN3-4.1, JP3.18, L1-V1.9, SIDE1.2
V2: IN3-4.16, JP4.18, L2-V2.9, SIDE2.32
V3: IN3-1.16, JP8.18, L2-V1.9, SIDE3.32
V4: IN3-1.1, JP5.18, L1-V2.9, SIDE4.2
V+: C6.1, C8.1, C14.1, D13.A, E1.7, E2.7, E3.14, R20.1, R25.1, R27.1, R31.1, R32.1, U$11.A2
V-: C5.1, C16.2, D5.A, E1.4, E2.4, R19.2, R21.2
VCC: A2-K2.18, BYP1.1, BYP2.1, BYP3.1, BYP4.1, BYP5.1, BYP6.1, BYP7.1, BYP8.1, BYP9.1, BYP10.1, IC1.14, IC2.14, IC3.14, IC4.14, IC5.14, IC6.14, IC7.14, IC8.14, IC9.1, IC9.2, IC9.3, IC9.13, IC9.14, JP2.1, POWER.2, POWER2.2, RN1.1, RN2.1, RN3.1, RN4.1
VCC1: A2-K1.18, BYP11.1, BYP12.1, BYP13.1, BYP14.1, BYP15.1, BYP16.1, BYP17.1, BYP18.1, BYP19.1, BYP20.1, IC10.14, IC11.14, IC12.14, IC13.14, IC14.14, IC15.14, IC16.14, IC17.14, IC18.1, IC18.2, IC18.3, IC18.13, IC18.14, JP7.1, POWER1.2, POWER3.2, RN5.1, RN6.1, RN7.1, RN8.1
VCC2: IC19.14, PAD16.1
VCC3: IC20.14, PAD28.1

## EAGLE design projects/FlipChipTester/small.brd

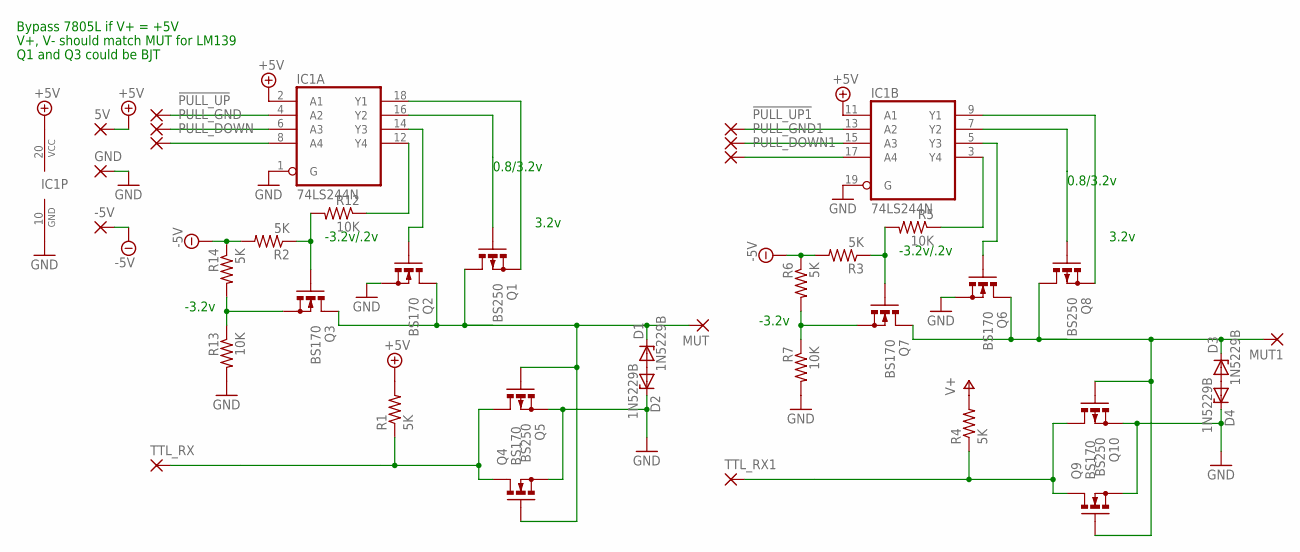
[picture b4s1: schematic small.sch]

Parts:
5V: 1,6/0,9
!PULL_UP, !PULL_UP1: 1,6/0,9
-5V: 1,6/0,9
D1, D2, D3, D4: 1N5229B; DO35Z10
GND: 1,6/0,9
IC1: 74LS244N; DIL20
MUT, MUT1: 1,6/0,9
PULL_DOWN, PULL_DOWN1: 1,6/0,9
PULL_GND, PULL_GND1: 1,6/0,9
Q1, Q5, Q8, Q10: BS250; SOT54E
Q2, Q3, Q4, Q6, Q7, Q9: BS170; SOT54E
R1, R2, R3, R4, R6, R14: 5K; 0207/10
R5, R7, R12, R13: 10K; 0207/10
TTL_RX, TTL_RX1: 1,6/0,9

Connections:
+5V: 5V.1, IC1.2 (A1), IC1.11 (A1), IC1.20 (VCC), R1.2
-5V: -5V.1, R2.2, R3.2, R6.1, R14.1
GND: D2.C, D4.C, GND.1, IC1.1 (G), IC1.10 (GND), IC1.19 (G), Q2.S, Q4.S, Q5.S, Q6.S, Q9.S, Q10.S, R7.2, R13.2
unnamed: D1.C, MUT.1, Q1.D, Q2.D, Q3.D, Q4.G, Q5.G
unnamed: Q3.G, R2.1, R12.2
unnamed: IC1.6 (A3), PULL_GND.1
unnamed: IC1.8 (A4), PULL_DOWN.1
unnamed: IC1.18 (Y1), Q1.S
unnamed: IC1.16 (Y2), Q1.G
unnamed: D1.A, D2.A
unnamed: Q4.D, Q5.D, R1.1, TTL_RX.1
unnamed: IC1.12 (Y4), R12.1
unnamed: !PULL_UP.1, IC1.4 (A2)
unnamed: IC1.14 (Y3), Q2.G
unnamed: IC1.15 (A3), PULL_GND1.1
unnamed: IC1.17 (A4), PULL_DOWN1.1
unnamed: Q7.G, R3.1, R5.2
unnamed: Q7.S, R6.2, R7.1
unnamed: Q3.S, R13.1, R14.2
unnamed: IC1.9 (Y1), Q8.S
unnamed: D3.C, MUT1.1, Q6.D, Q7.D, Q8.D, Q9.G, Q10.G
unnamed: !PULL_UP1.1, IC1.13 (A2)
unnamed: D3.A, D4.A
unnamed: Q9.D, Q10.D, R4.1, TTL_RX1.1
unnamed: IC1.7 (Y2), Q8.G
unnamed: IC1.3 (Y4), R5.1
unnamed: IC1.5 (Y3), Q6.G
V+: R4.2

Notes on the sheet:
V+, V- should match MUT for LM139
Bypass 7805L if V+ = +5V
-3.2v
-3.2v/.2v
3.2v
0.8/3.2v
Q1 and Q3 could be BJT

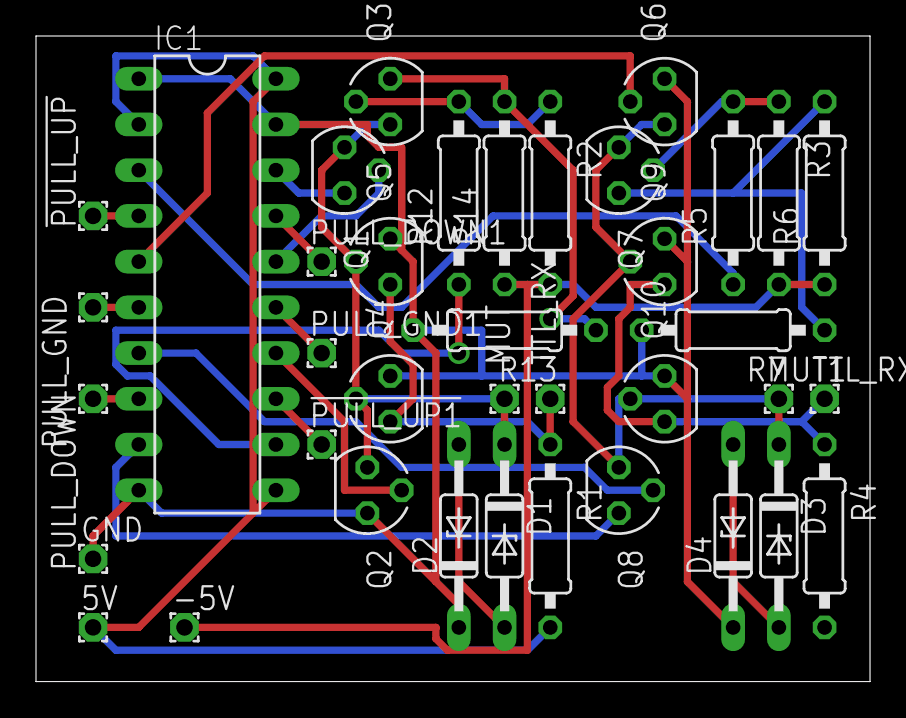
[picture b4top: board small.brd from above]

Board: 2 copper layers, 46.3 x 35.9 mm, 38 parts (0 on the bottom side), 27 nets.

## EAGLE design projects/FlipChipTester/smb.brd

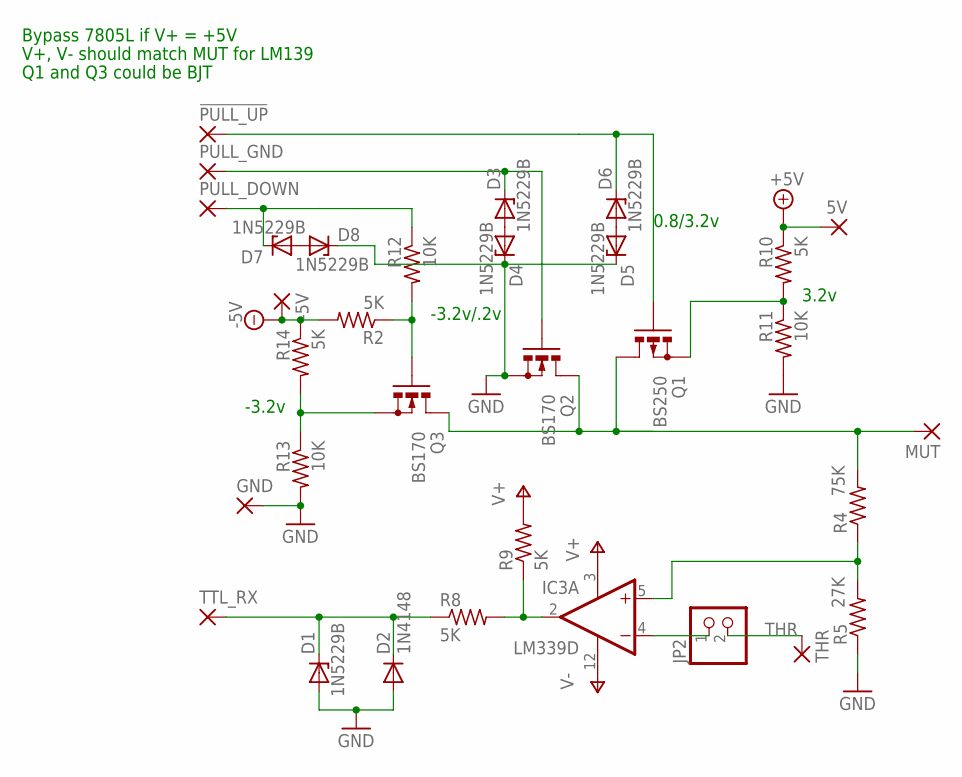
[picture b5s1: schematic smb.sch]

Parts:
5V: 1,6/0,9
!PULL_UP: 1,6/0,9
-5V: 1,6/0,9
D1, D3, D4, D5, D6, D7, D8: 1N5229B; SOD80C
D2: 1N4148; SOD80C
GND: 1,6/0,9
IC3: LM339D; SO14
JP2: PINHD-1X2; 1X02
MUT: 1,6/0,9
PULL_DOWN: 1,6/0,9
PULL_GND: 1,6/0,9
Q1: BS250; SOT54E
Q2, Q3: BS170; SOT54E
R2, R8, R9, R10, R14: 5K; M1206
R4: 75K; M1206
R5: 27K; M1206
R11, R12, R13: 10K; M1206
THR: 1,6/0,9
TTL_RX: 1,6/0,9

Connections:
+5V: 5V.1, R10.1
-5V: -5V.1, R2.2, R14.1
GND: D1.A, D2.A, D4.C, D5.C, D8.C, GND.1, Q2.S, R5.1, R11.2, R13.2
unnamed: MUT.1, Q1.D, Q2.D, Q3.D, R4.2
unnamed: Q3.G, R2.1, R12.2
unnamed: D3.C, PULL_GND.1, Q2.G
unnamed: D7.C, PULL_DOWN.1, R12.1
unnamed: Q1.S, R10.2, R11.1
unnamed: D5.A, D6.A
unnamed: IC3.5 (+IN), R4.1, R5.2
unnamed: IC3.4 (-IN), JP2.1
unnamed: IC3.2 (OUT), R8.2, R9.1
unnamed: !PULL_UP.1, D6.C, Q1.G
unnamed: D3.A, D4.A
unnamed: D1.C, D2.C, R8.1, TTL_RX.1
unnamed: D7.A, D8.A
unnamed: Q3.S, R13.1, R14.2
THR: JP2.2, THR.1
V+: IC3.3 (V+), R9.2
V-: IC3.12 (GND)

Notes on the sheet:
V+, V- should match MUT for LM139
Bypass 7805L if V+ = +5V
-3.2v
-3.2v/.2v
3.2v
0.8/3.2v
Q1 and Q3 could be BJT

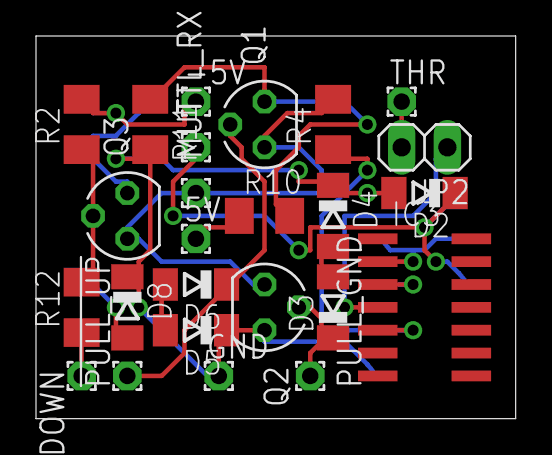
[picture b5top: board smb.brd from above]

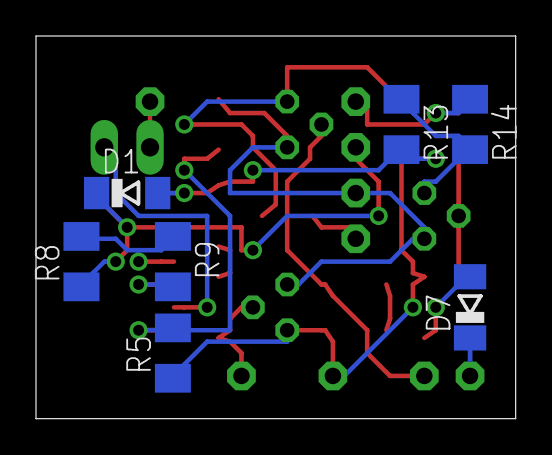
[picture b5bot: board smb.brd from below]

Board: 2 copper layers, 26.7 x 21.3 mm, 32 parts (7 on the bottom side), 19 nets.
